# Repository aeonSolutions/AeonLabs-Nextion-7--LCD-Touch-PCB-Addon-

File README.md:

[PCB-Prototyping-Catalogue](https://github.com/aeonSolutions/PCB-Prototyping-Catalogue)  >>  [Smart LCD Touch Displays](https://github.com/aeonSolutions/PCB-Prototyping-Catalogue/tree/main/Smart%20LCD%20Touch%20Displays)  >>  AeonLabs Nextion 7" LCD Touch PCB Addon

<br>

<p align="right">
    sponsored by <br>
    
</p>

# AeonLabs Nextion 7" LCD Touch PCB Addon 
This repo contains the KiCad files for the  WIFI &amp; BLE addon for Nextion 7" LCD Touch. This PCB adds WiFi and BLE capabilities to stock Nextion 7" LCDs (http://www.nextion.tech). Features WIFI, Bluetooth a RGB LED and a Buzzer and is designed to be mounted on top of existing Nextion PCB board. Optionally:
- can be installed with a RFID RC522 module for contactless read / write capabilities.
- can be installed a barcode & QR code wireless module for handheld barcode & QR code scanners

*Don't forget to LIKE , SHARE and subscribe the free whatsApp group* and if you liked this PCB consider buying me a cup of coffee. Links below.

### Status
  Powers up. Waiting to be tested.

If you already tested this PCB send me a message. Thank you

## Revisions
- revision 3.1
  - added barcode & QR code 2.4G wireless module for handheld barcode & QR code scanners
  - minor bug corrections to the PCB
  
- revision 2.4
  - added wired power source conenction for 5V to 12V 1A power input for industrial applications. 

PCB fabrication of June 2022 (reviision 3.1) was sponsored by [PCBWay](www.pcbway.com)

## Download options
Download this repository if you need the KiCad Files. or, download the Gerber files in the release section of this repository

## Liked it ? Get a Free PCB for yourself
Send me your Device or hardware and i will design a custom PCB for it. Free of charge. Contact-me on WhatsApp or email for more info. 

## Q&A WhatsApp Group
If you have any Questions or simply  like this kind of projects and want to stay updated with the latest research ideas and prototypes during the day and week, join the WhatsApp Group
[A.I. Things](https://chat.whatsapp.com/FkNC7u83kuy2QRA5sqjBVg)

## Fully assembled PCB
Alternatively, and if you do not want to build a PCB by yourself and like to buy one:

The price starts at 30eur plus postage fees.
(I will also deliver the assembled PCB with all the components in place at a fair aditonal cost).

## Nextion LCDs
If you like this , but on another NEXTION LCD TOUCH, drop me a DM on whatsApp [here](https://chat.whatsapp.com/FkNC7u83kuy2QRA5sqjBVg) and i will do for free the KiCad design for you.

#### Be supportive of my dedication and work towards technology education and buy me a coffee. Link below.

________________________________________________________________________________________________________________

## PCB Parts list
- DC2DC converter HX4002B x2 : https://s.click.aliexpress.com/e/_Ak7IPx
- Capacitor 100nF SMD 1206 : https://s.click.aliexpress.com/e/_AVdmzr
- Capacitor 2.2uF SMD 1206 : https://s.click.aliexpress.com/e/_AVdmzr
- Resistor SMD 1206 330R x3 : https://s.click.aliexpress.com/e/_A7OXrR
- ESP32 WROOM32 x1 : https://s.click.aliexpress.com/e/_AF7N6l
- Buzzer x1: https://s.click.aliexpress.com/e/_AF7N6l
- LED RGB x1: https://s.click.aliexpress.com/e/_AccXHT
- RFID RC522 x1 (optional) : https://s.click.aliexpress.com/e/_Am0LAH
- 

## Firmware Download 
one can use the PCB in the repository [AeonLabs-MCU-Burner-USB-to-UART-TTL](https://github.com/aeonSolutions/AeonLabs-MCU-Burner-USB-to-UART-TTL) to program the ESP32 WROOM32 MCU on this PCB.

<br />
<br />

______________________________________________________________________________________________________________________________

### PCB Conceptualization and Design
<p align="center">

</p>

<br />
<br />

### PCB Fabrication
<p align="center">

</p>

<br />
<br />

## Author

You can get in touch with me on my LinkedIn Profile:

#### Miguel Tomas

You can also follow my GitHub Profile to stay updated about my latest projects: 

<br>

### Be supportive of my dedication and work towards technology education and buy me a cup of coffee
The PCB Desgin Files i provide here for anyone to use are free. If you like this Smart Device or use it, please consider buying me a cup of coffee, a slice of pizza or a book to help me study, eat and think new PCB design files.

<p align+"left">

<br>

</p>

<br />

### Make a donation on Paypal
Make a donation on paypal and get a TAX refund*.

<br>

### Support all these open hardware projects and become a patreon  
Liked any of my PCB KiCad Designs? Help and Support my open work to all by becomming a LDAD Patreon.
In return I will give a free PCB design in KiCad to all patreon supporters. To learn more go to patreon.com. Link below.

<br />
<br />

______________________________________________________________________________________________________________________________
### License

Before proceeding to download any of AeonLabs software solutions for open-source development and/or PCB hardware electronics development make sure you are choosing the right license for your project. See [AeonLabs Solutions for Open Hardware & Source Development](https://github.com/aeonSolutions/PCB-Prototyping-Catalogue/wiki/AeonLabs-Solutions-for-Open-Hardware-&-Source-Development) for more information. 

______________________________________________________________________________________________________________________________

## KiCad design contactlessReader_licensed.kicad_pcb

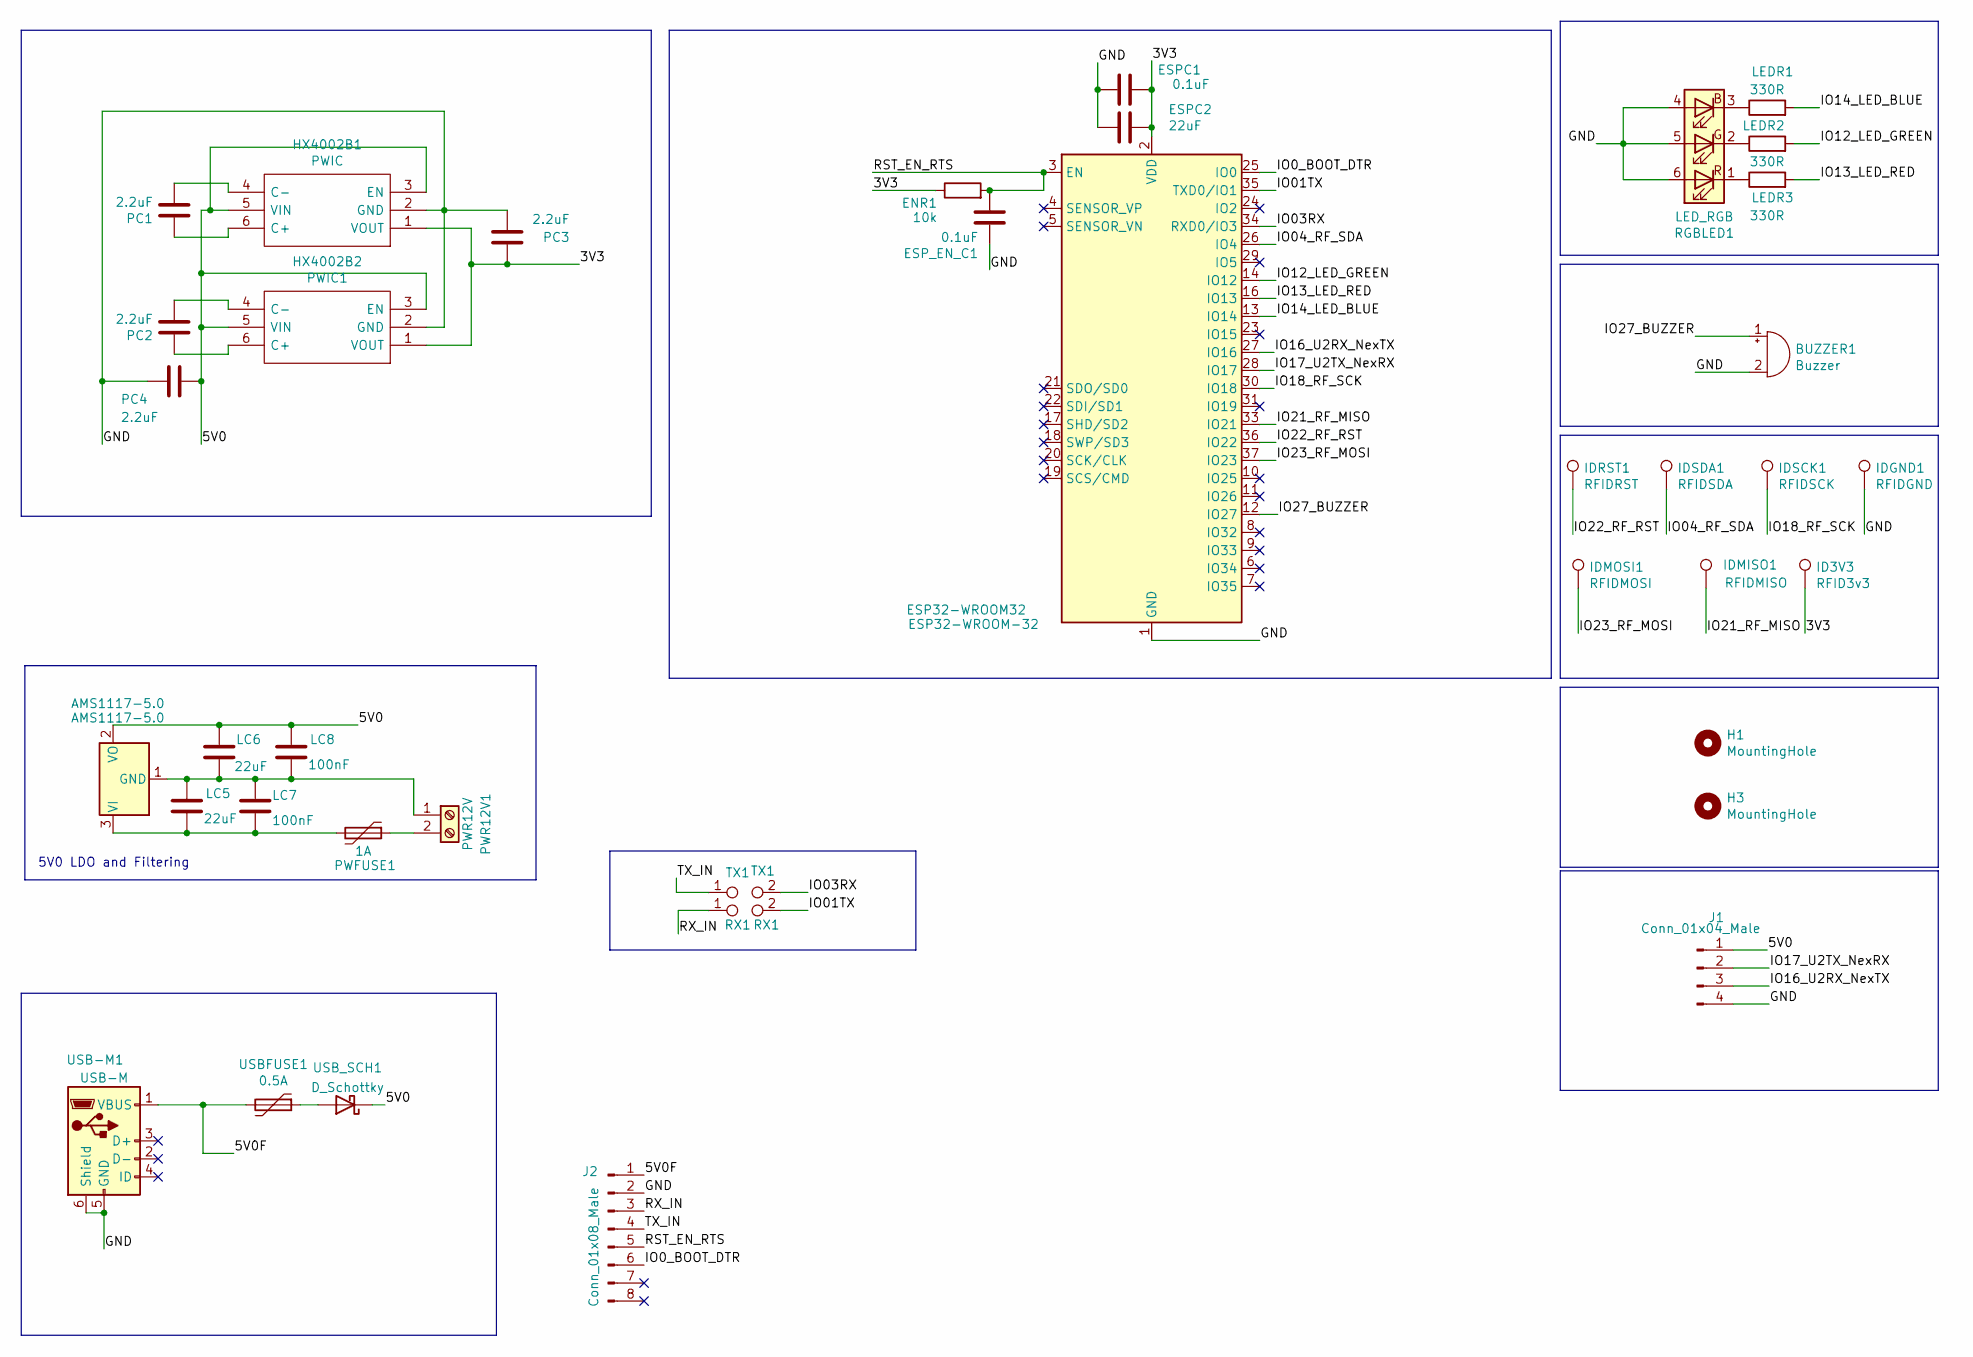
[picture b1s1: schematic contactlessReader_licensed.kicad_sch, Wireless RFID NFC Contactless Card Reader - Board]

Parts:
AMS1117-5.0: AMS1117-5.0; SOT-223-3_TabPin2
BUZZER1: Buzzer; MagneticBuzzer_Kobitone_254-EMB84Q-RO
ENR1: 10k; R_1206_3216Metric
ESP32-WROOM32: ESP32-WROOM-32
ESPC1: 0.1uF; C_1206_3216Metric
ESPC2: 22uF; C_1206_3216Metric
ESP_EN_C1: 0.1uF; C_1206_3216Metric
H1, H3: MountingHole; MountingHole_3.2mm_M3_DIN965
HX4002B1: PWIC; HX4002 SOT95 P280X125-6N; Manufacturer_Part_Number HX4002
HX4002B2: PWIC1; HX4002 SOT95 P280X125-6N; Manufacturer_Part_Number HX4002
ID3V3: RFID3v3; TestPoint_THTPad_2.0x2.0mm_Drill1.0mm
IDGND1: RFIDGND; TestPoint_THTPad_2.0x2.0mm_Drill1.0mm
IDMISO1: RFIDMISO; TestPoint_THTPad_2.0x2.0mm_Drill1.0mm
IDMOSI1: RFIDMOSI; TestPoint_THTPad_2.0x2.0mm_Drill1.0mm
IDRST1: RFIDRST; TestPoint_THTPad_2.0x2.0mm_Drill1.0mm
IDSCK1: RFIDSCK; TestPoint_THTPad_2.0x2.0mm_Drill1.0mm
IDSDA1: RFIDSDA; TestPoint_THTPad_2.0x2.0mm_Drill1.0mm
J1: Conn_01x04_Male; PinHeader_1x04_P2.54mm_Vertical
J2: Conn_01x08_Male; SOIC_clipProgSmall
LC5, LC6: 22uF; C_1206_3216Metric_Pad1.33x1.80mm_HandSolder
LC7, LC8: 100nF; C_1206_3216Metric_Pad1.33x1.80mm_HandSolder
LEDR1, LEDR2, LEDR3: 330R; R_1206_3216Metric
PC1, PC2, PC3, PC4: 2.2uF; C_1206_3216Metric
PWFUSE1: 1A; Fuse_1206_3216Metric
PWR12V1: PWR12V; TerminalBlock_4Ucon_1x02_P3.50mm_Vertical
RGBLED1: LED_RGB; LED_RGB_5050-6
RX1: RX1; TestPoint_Pad_Bridge_1.0x1.0mm
TX1: TX1; TestPoint_Pad_Bridge_1.0x1.0mm
USB-M1: USB-M; Micro_USB_pcb_socket_5pin_4weld_points
USBFUSE1: 0.5A; Fuse_1206_3216Metric
USB_SCH1: D_Schottky; D_1210_3225Metric_Pad1.42x2.65mm_HandSolder

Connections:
/3V3: ENR1.1, ESP32-WROOM32.2 (VDD), ESPC1.1, ESPC2.1, HX4002B1.1 (VOUT), HX4002B2.1 (VOUT), ID3V3.1, PC3.1
/5V0: AMS1117-5.0.2 (VO), HX4002B1.3 (EN), HX4002B1.5 (VIN), HX4002B2.3 (EN), HX4002B2.5 (VIN), J1.1, LC6.1, LC8.1, PC4.1, USB_SCH1.1 (K)
/5V0F: J2.1, USB-M1.1 (VBUS), USBFUSE1.2
/GND: BUZZER1.2 (+), ESP32-WROOM32.1 (GND), ESP32-WROOM32.15 (GND), ESP32-WROOM32.38 (GND), ESP32-WROOM32.39 (GND), ESPC1.2, ESPC2.2, ESP_EN_C1.1, HX4002B1.2 (GND), HX4002B2.2 (GND), IDGND1.1, J1.4, J2.2, PC3.2, PC4.2, RGBLED1.4 (BA), RGBLED1.5 (GA), RGBLED1.6 (RA), USB-M1.5 (GND), USB-M1.6 (Shield)
/IO0_BOOT_DTR: ESP32-WROOM32.25 (IO0), J2.6
/IO01TX: ESP32-WROOM32.35 (TXD0/IO1), RX1.2
/IO03RX: ESP32-WROOM32.34 (RXD0/IO3), TX1.2
/IO04_RF_SDA: ESP32-WROOM32.26 (IO4), IDSDA1.1
/IO12_LED_GREEN: ESP32-WROOM32.14 (IO12), LEDR2.2
/IO13_LED_RED: ESP32-WROOM32.16 (IO13), LEDR3.2
/IO14_LED_BLUE: ESP32-WROOM32.13 (IO14), LEDR1.2
/IO16_U2RX_NexTX: ESP32-WROOM32.27 (IO16), J1.3
/IO17_U2TX_NexRX: ESP32-WROOM32.28 (IO17), J1.2
/IO18_RF_SCK: ESP32-WROOM32.30 (IO18), IDSCK1.1
/IO21_RF_MISO: ESP32-WROOM32.33 (IO21), IDMISO1.1
/IO22_RF_RST: ESP32-WROOM32.36 (IO22), IDRST1.1
/IO23_RF_MOSI: ESP32-WROOM32.37 (IO23), IDMOSI1.1
/IO27_BUZZER: BUZZER1.1 (-), ESP32-WROOM32.12 (IO27)
/RST_EN_RTS: ENR1.2, ESP32-WROOM32.3 (EN), ESP_EN_C1.2, J2.5
/RX_IN: J2.3, RX1.1
/TX_IN: J2.4, TX1.1
unnamed: AMS1117-5.0.1 (GND), LC5.1, LC6.2, LC7.1, LC8.2, PWR12V1.1
unnamed: AMS1117-5.0.3 (VI), LC5.2, LC7.2, PWFUSE1.2
unnamed: HX4002B1.4 (C-), PC1.2
unnamed: HX4002B1.6 (C+), PC1.1
unnamed: HX4002B2.4 (C-), PC2.2
unnamed: HX4002B2.6 (C+), PC2.1
unnamed: LEDR1.1, RGBLED1.3 (BK)
unnamed: LEDR2.1, RGBLED1.2 (GK)
unnamed: LEDR3.1, RGBLED1.1 (RK)
unnamed: PWFUSE1.1, PWR12V1.2
unnamed: USBFUSE1.1, USB_SCH1.2 (A)

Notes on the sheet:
5V0 LDO and Filtering

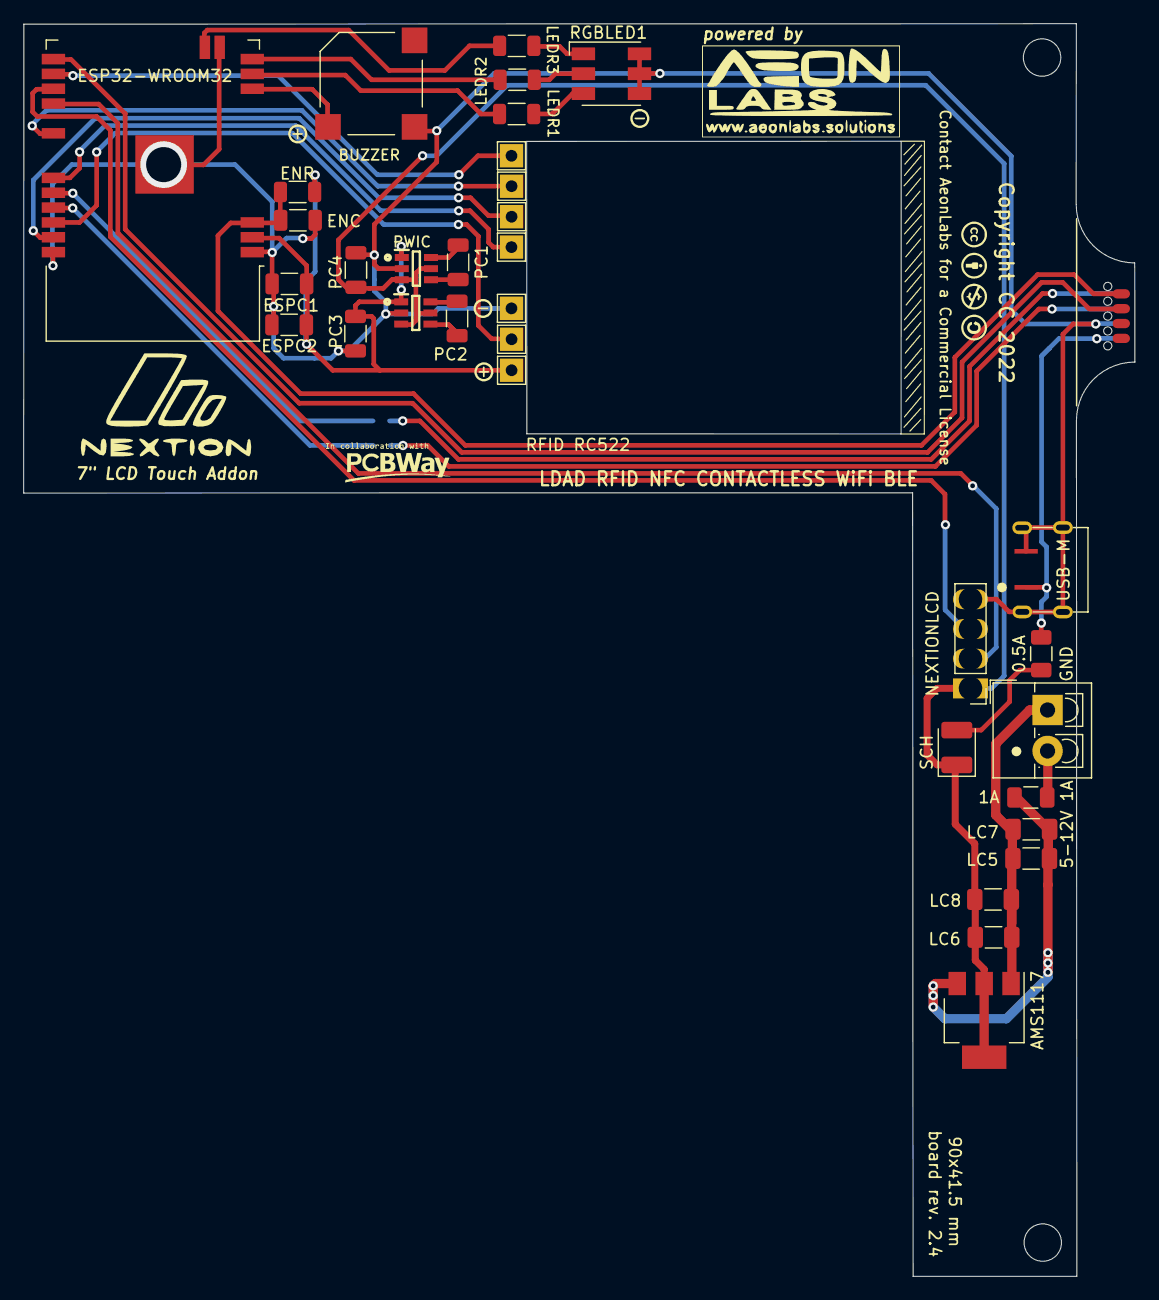
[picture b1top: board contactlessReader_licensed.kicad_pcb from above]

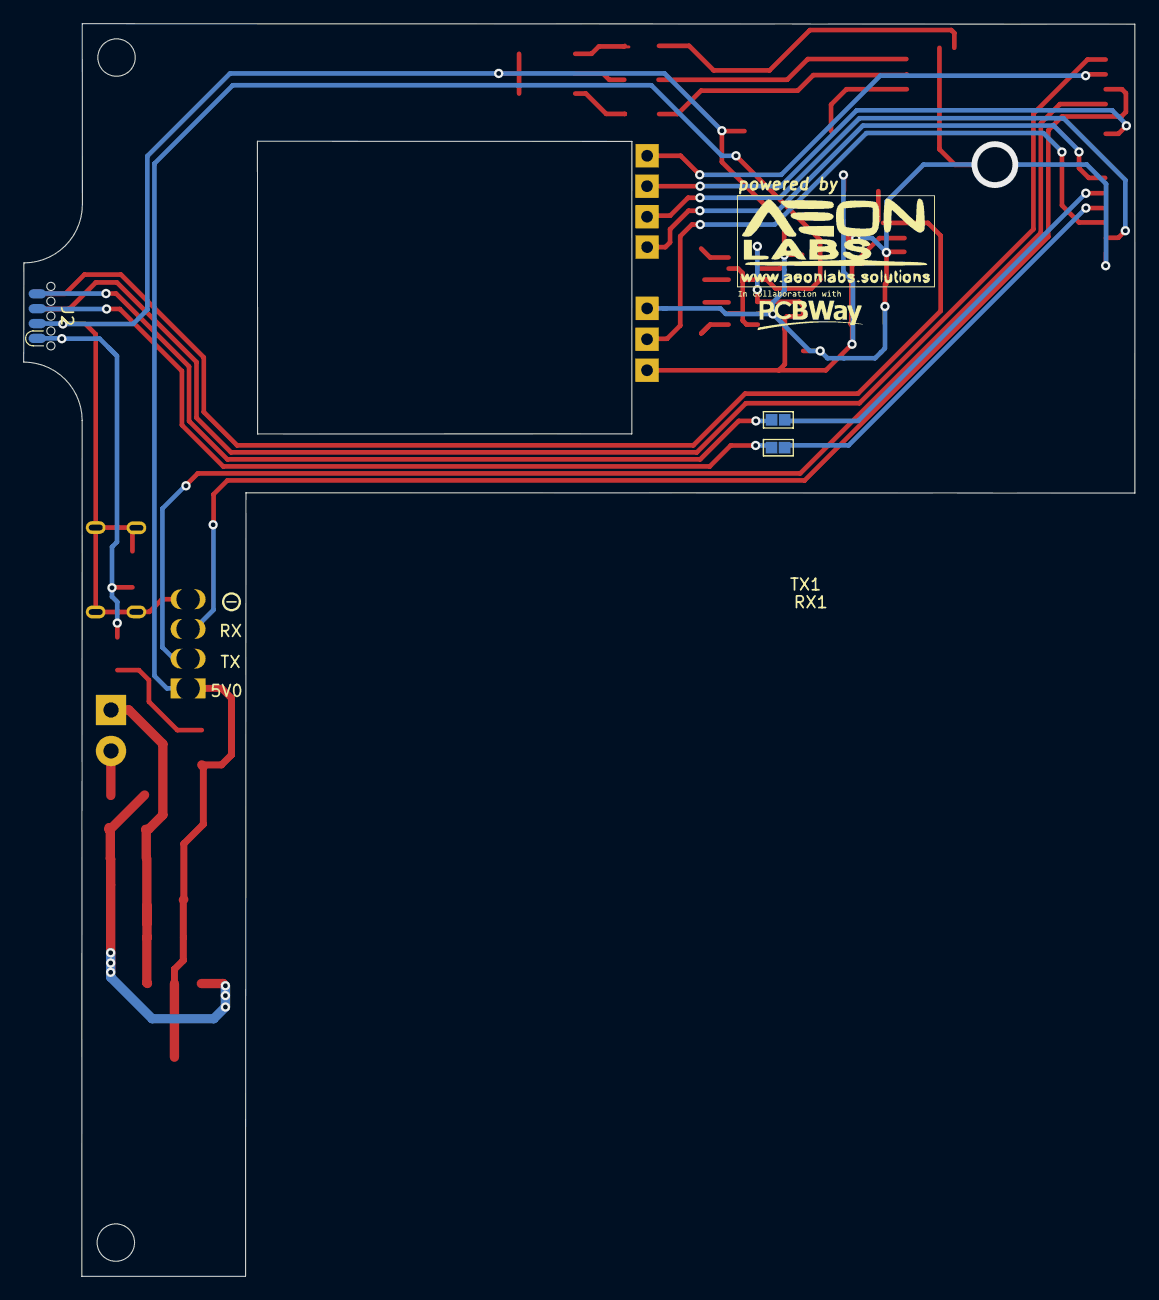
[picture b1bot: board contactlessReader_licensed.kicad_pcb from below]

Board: 2 copper layers, 95.0 x 107.1 mm, 39 parts (3 on the bottom side), 32 nets.

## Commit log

2022-04-01 initial commint
2022-04-23 rev. 2.4
2022-05-29 revision update

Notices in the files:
contactlessReader_licensed.kicad_pcb:
Copyright CC 2022
contactlessReader_licensed.kicad_sch:
Copyright 2022
